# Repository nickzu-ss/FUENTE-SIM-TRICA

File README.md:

# FUENTE-SIM-TRICA
Diseño de una fuente de alimentación simétrica de ±15 V, con esquemas, archivos de diseño, simulaciones y documentación técnica.

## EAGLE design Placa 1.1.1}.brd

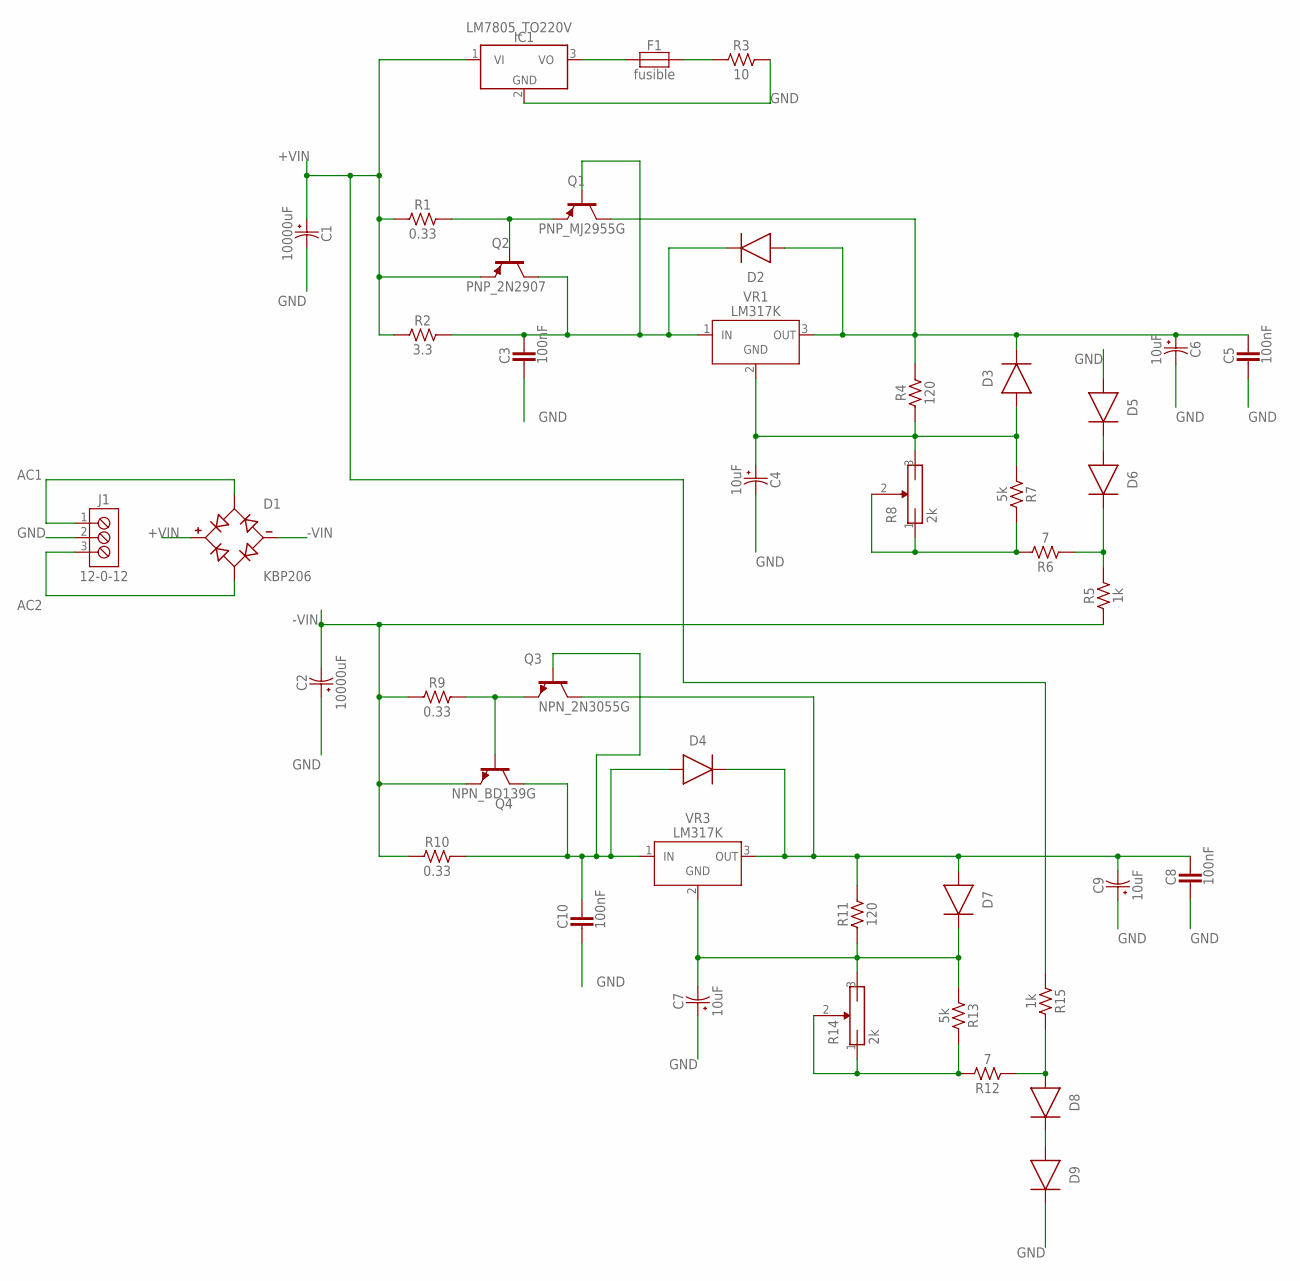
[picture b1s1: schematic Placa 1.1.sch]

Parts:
C1, C2: 10000uF; CAPPRD550W60D1200H2000B
C3, C5, C8, C10: 100nF; CAP-THRU-2.54MM
C4, C6, C7, C9: 10uF; CAPPRD250W80D630H800B
D1: KBP206; SIP380W81P386L1470H1270Q4
D2, D3, D4, D5, D6, D7, D8, D9: DIODEDIODE-AXIAL; DIODE-AXIAL
F1: fusible; FUSAD2590W70L2150D550B
IC1: LM7805_TO220V; TO220V
J1: 12-0-12; TERMBLK_508-3N
Q1: PNP_MJ2955G; TO92
Q2: PNP_2N2907; TO92
Q3: NPN_2N3055G; TO92
Q4: NPN_BD139G; TO92
R1, R9, R10: 0.33; RESAD724W46L381D178B
R2: 3.3; RESAD724W46L381D178B
R3: 10; RESAD724W46L381D178B
R4, R11: 120; RESAD724W46L381D178B
R5, R15: 1k; RESAD724W46L381D178B
R6, R12: 7; RESAD724W46L381D178B
R7, R13: 5k; RESAD724W46L381D178B
R8, R14: 2k; WH148-5.0
VR1, VR3: LM317K; TO220V

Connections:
+VIN: C1.1 (+), D1.1 (+), IC1.1 (VI), Q2.3 (E), R1.1, R2.1, R15.1
-VIN: C2.2 (-), D1.4 (-), Q4.1 (E), R5.1, R9.1, R10.1
AC1: D1.2 (AC1), J1.1
AC2: D1.3 (AC2), J1.3
GND: C1.2 (-), C2.1 (+), C3.2, C4.2 (-), C5.2, C6.2 (-), C7.1 (+), C8.2, C9.1 (+), C10.2, D5.1 (A), D9.2 (C), IC1.2 (GND), J1.2, R3.2
unnamed: C5.1, C6.1 (+), D2.1 (A), D3.2 (C), Q1.1 (C), R4.2, VR1.3 (VO)
unnamed: R6.2, R7.2, R8.1, R8.2 (W)
unnamed: Q1.3 (E), Q2.2 (B), R1.2
unnamed: C3.1, D2.2 (C), Q1.2 (B), Q2.1 (C), R2.2, VR1.1 (VI)
unnamed: C4.1 (+), D3.1 (A), R4.1, R7.1, R8.3, VR1.2 (GND)
unnamed: F1.1, IC1.3 (VO)
unnamed: D5.2 (C), D6.1 (A)
unnamed: D6.2 (C), R5.2, R6.1
unnamed: F1.2, R3.1
unnamed: Q3.1 (E), Q4.2 (B), R9.2
unnamed: C8.1, C9.2 (-), D4.2 (C), D7.1 (A), Q3.3 (C), R11.2, VR3.3 (VO)
unnamed: C10.1, D4.1 (A), Q3.2 (B), Q4.3 (C), R10.2, VR3.1 (VI)
unnamed: C7.2 (-), D7.2 (C), R11.1, R13.1, R14.3, VR3.2 (GND)
unnamed: R12.2, R13.2, R14.1, R14.2 (W)
unnamed: D8.2 (C), D9.1 (A)
unnamed: D8.1 (A), R12.1, R15.2

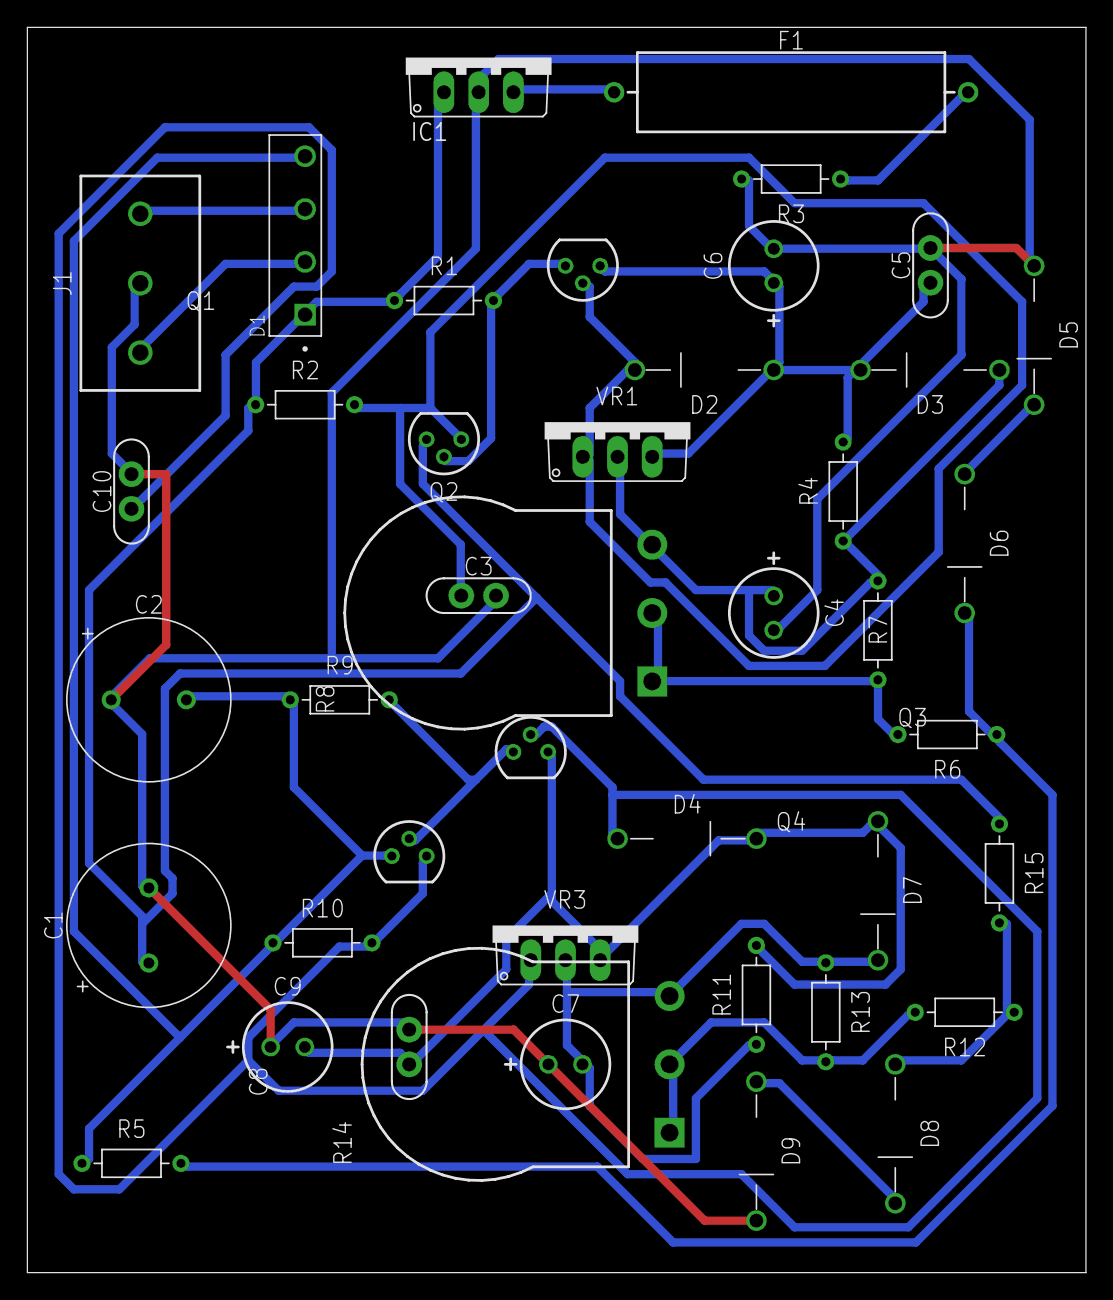
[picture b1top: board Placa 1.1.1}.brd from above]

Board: 2 copper layers, 77.5 x 91.1 mm, 43 parts (0 on the bottom side), 21 nets.
